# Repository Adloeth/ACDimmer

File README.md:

# ACDimmer

This is my first PCB design using mains. It's purpose is to lower the power delivered to heating resistors from a toaster oven in order to make my own reflow oven that will go with a future PnP machine project.

AC Dimmers already exist on the market, most of them doesn't work with mains and the others use a potentiometer to control the TRIAC. I obviously need a microcontroller to manage the TRIAC so the solder profile can be correctly followed.

Seeing that these are difficult to find, I decided to make my own.

## The Board

The board works as a passthrough for mains so I don't need to use lever wire connectors for the ground and neutral. For a DIY reflow oven, a toaster oven of 1500W is recommended, so the board is made to handle a maximum of 7A (around 1600W) (as such, it needs 2 oz/ft² of copper) limited by a fuse at the start of the circuit. The circuit is then splitted, one part goes for the two TRIACs (one of them is the optocoupler that controls the main TRIAC) and the other is for a zero crossing detector to synchronize the microcontroller with mains frequency.

I am well aware of the dangers of mains, so I made sure the clearances were correct, there is a clear separation from the high voltage and low voltage parts of the PCB (linked by optocouplers), the whole PCB is grounded and although the TRIAC datasheet recommends using capacitors (to absorb inrush currents that mostly appear at 50% power), they can be very dangerous and they are not really necessary as there are no sensible components in the circuit (which consist only of a few heating resistors in series). I also plan to 3D print a case with a fire retardant filament, we never know.

All components are THT so I can solder them by hand easily, I might make a V2.0 with SMD components later, I need this one first because I need a reflow oven to reflow the PCB with SMD components for the reflow oven... .

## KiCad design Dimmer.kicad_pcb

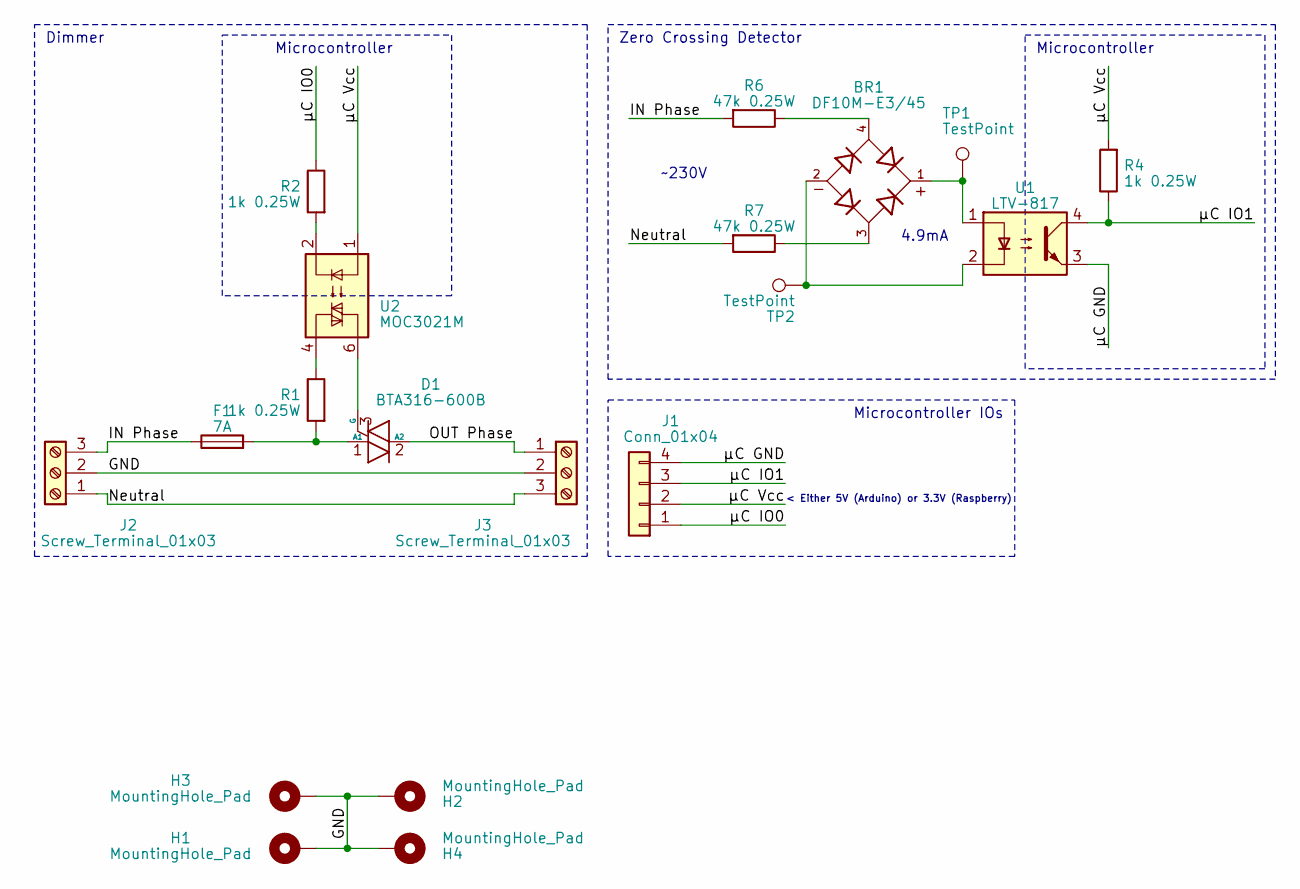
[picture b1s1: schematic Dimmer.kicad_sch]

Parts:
BR1: DF10M-E3/45; DIP797W52P510L831H533Q4; PARTREV 03-Sep-2020
D1: BTA316-600B; TO-220-3_Vertical_Stagger
F1: 7A; 0751.0231Schurter
H1, H2, H3, H4: MountingHole_Pad; MountingHole_2.2mm_M2_DIN965_Pad
J1: Conn_01x04; JST_EH_S4B-EH_1x04_P2.50mm_Horizontal
J2, J3: Screw_Terminal_01x03; TerminalBlock_Phoenix_PT-1,5-3-3.5-H_1x03_P3.50mm_Horizontal
R1, R2, R4: 1k 0.25W; R_Axial_DIN0207_L6.3mm_D2.5mm_P10.16mm_Horizontal
R6, R7: 47k 0.25W; R_Axial_DIN0207_L6.3mm_D2.5mm_P10.16mm_Horizontal
TP1, TP2: TestPoint; TestPoint_Pad_D2.0mm
U1: LTV-817; DIP-4_W7.62mm
U2: MOC3021M; DIP-6_W10.16mm

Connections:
/GND: H1.1, H2.1, H3.1, H4.1, J2.2, J3.2
/IN Phase: F1.1, J2.3, R6.2
/Neutral: J2.1, J3.3, R7.2
/OUT Phase: D1.2 (A2), J3.1
/µC GND: J1.4, U1.3
/µC IO0: J1.1, R2.1
/µC IO1: J1.3, R4.1, U1.4
/µC Vcc: J1.2, R4.2, U2.1
unnamed: BR1.1, TP1.1, U1.1
unnamed: BR1.2, TP2.1, U1.2
unnamed: BR1.3, R7.1
unnamed: BR1.4, R6.1
unnamed: D1.1 (A1), F1.2, R1.2
unnamed: D1.3 (G), U2.6
unnamed: R1.1, U2.4
unnamed: R2.2, U2.2

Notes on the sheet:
Microcontroller
< Either 5V (Arduino) or 3.3V (Raspberry)
Dimmer
~230V
Microcontroller IOs
Zero Crossing Detector
4.9mA

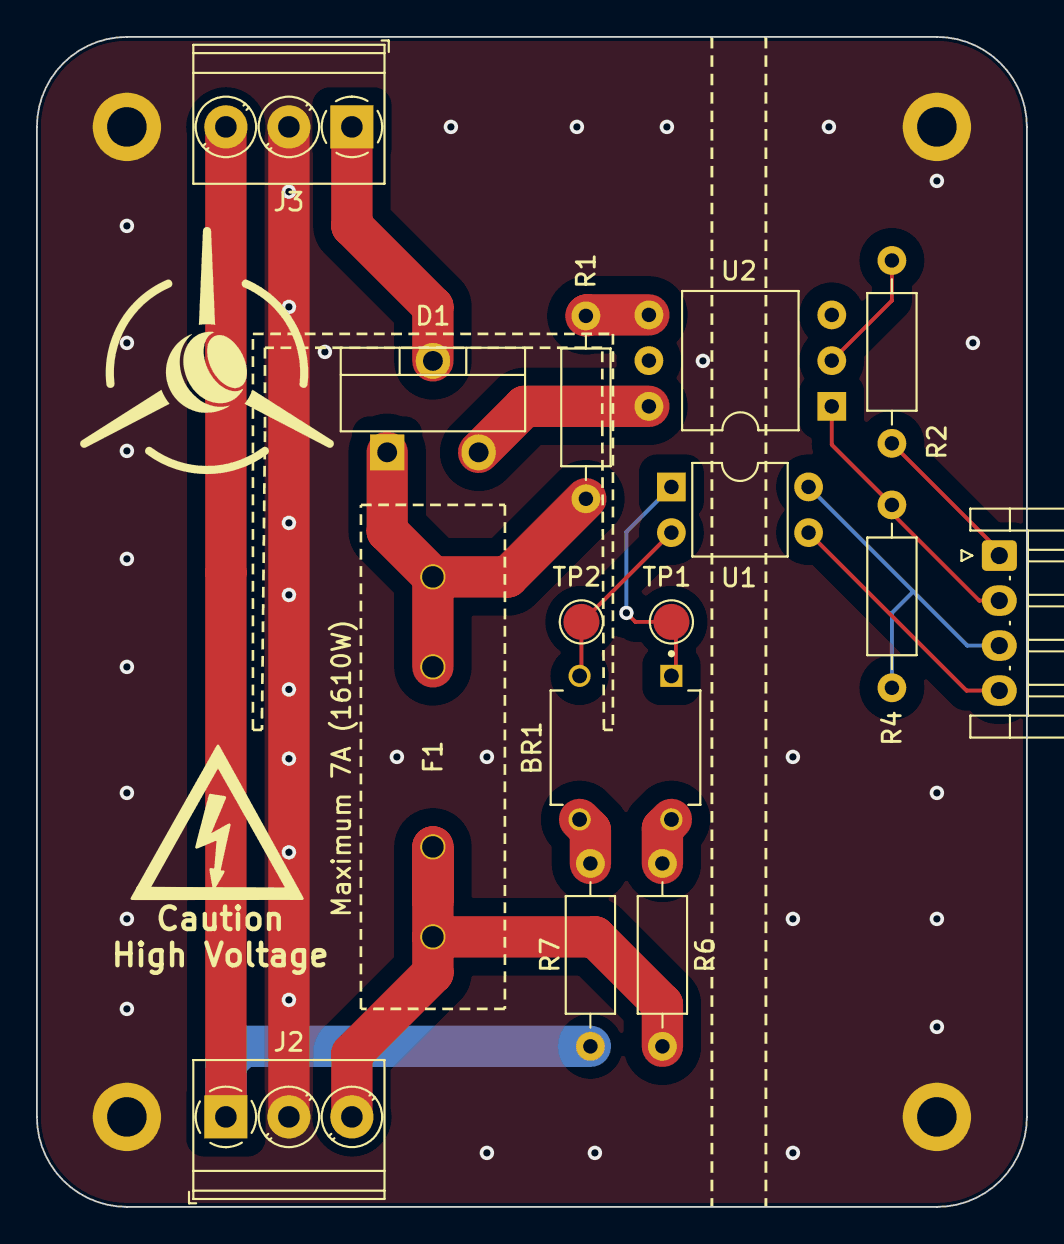
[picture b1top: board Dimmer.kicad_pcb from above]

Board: 2 copper layers, 55.0 x 65.0 mm, 19 parts (0 on the bottom side), 16 nets.
